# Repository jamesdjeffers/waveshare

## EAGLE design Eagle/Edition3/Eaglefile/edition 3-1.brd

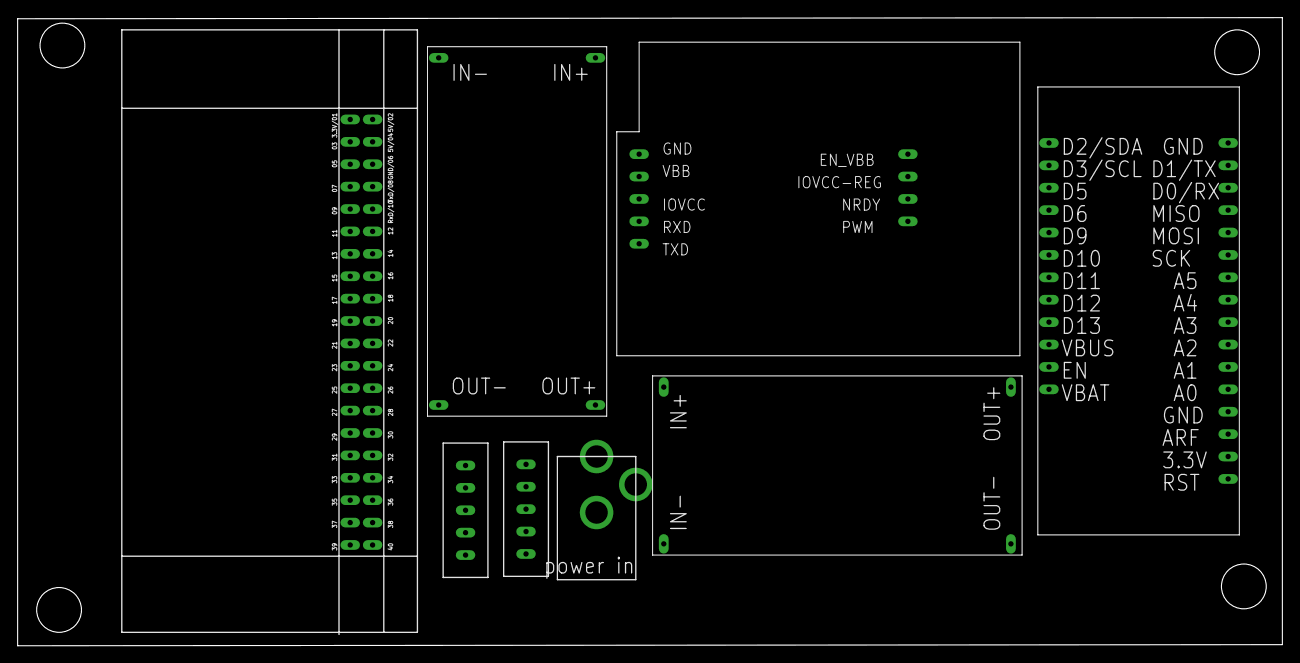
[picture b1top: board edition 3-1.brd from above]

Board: 2 copper layers, 143.4 x 71.2 mm, 8 parts (0 on the bottom side), 10 nets, no tracks yet.

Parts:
DCDC1, DCDC2: DCDC
FEATHER1: FEATHER
K96SENSOR1: K96SENSOR
PIN1, PIN2: PIN
U$1: POWER; POWERIN
U$2: RASPBERRYPI

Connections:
unnamed: DCDC1.P$2, DCDC2.P$2, K96SENSOR1.P$2, PIN1.P$1, U$1.P$1
unnamed: DCDC1.P$1, DCDC1.P$4, DCDC2.P$1, DCDC2.P$4, FEATHER1.P$13, K96SENSOR1.P$1, PIN1.P$2, U$1.P$2, U$1.P$3, U$2.P$3
unnamed: FEATHER1.P$6, K96SENSOR1.P$4
unnamed: DCDC1.P$3, FEATHER1.P$12
unnamed: FEATHER1.P$7, K96SENSOR1.P$5
unnamed: FEATHER1.P$4, K96SENSOR1.P$8
unnamed: FEATHER1.P$9, PIN2.P$1, U$2.P$5
unnamed: FEATHER1.P$3, K96SENSOR1.P$6
unnamed: FEATHER1.P$27, K96SENSOR1.P$3
unnamed: FEATHER1.P$8, PIN2.P$2, U$2.P$4

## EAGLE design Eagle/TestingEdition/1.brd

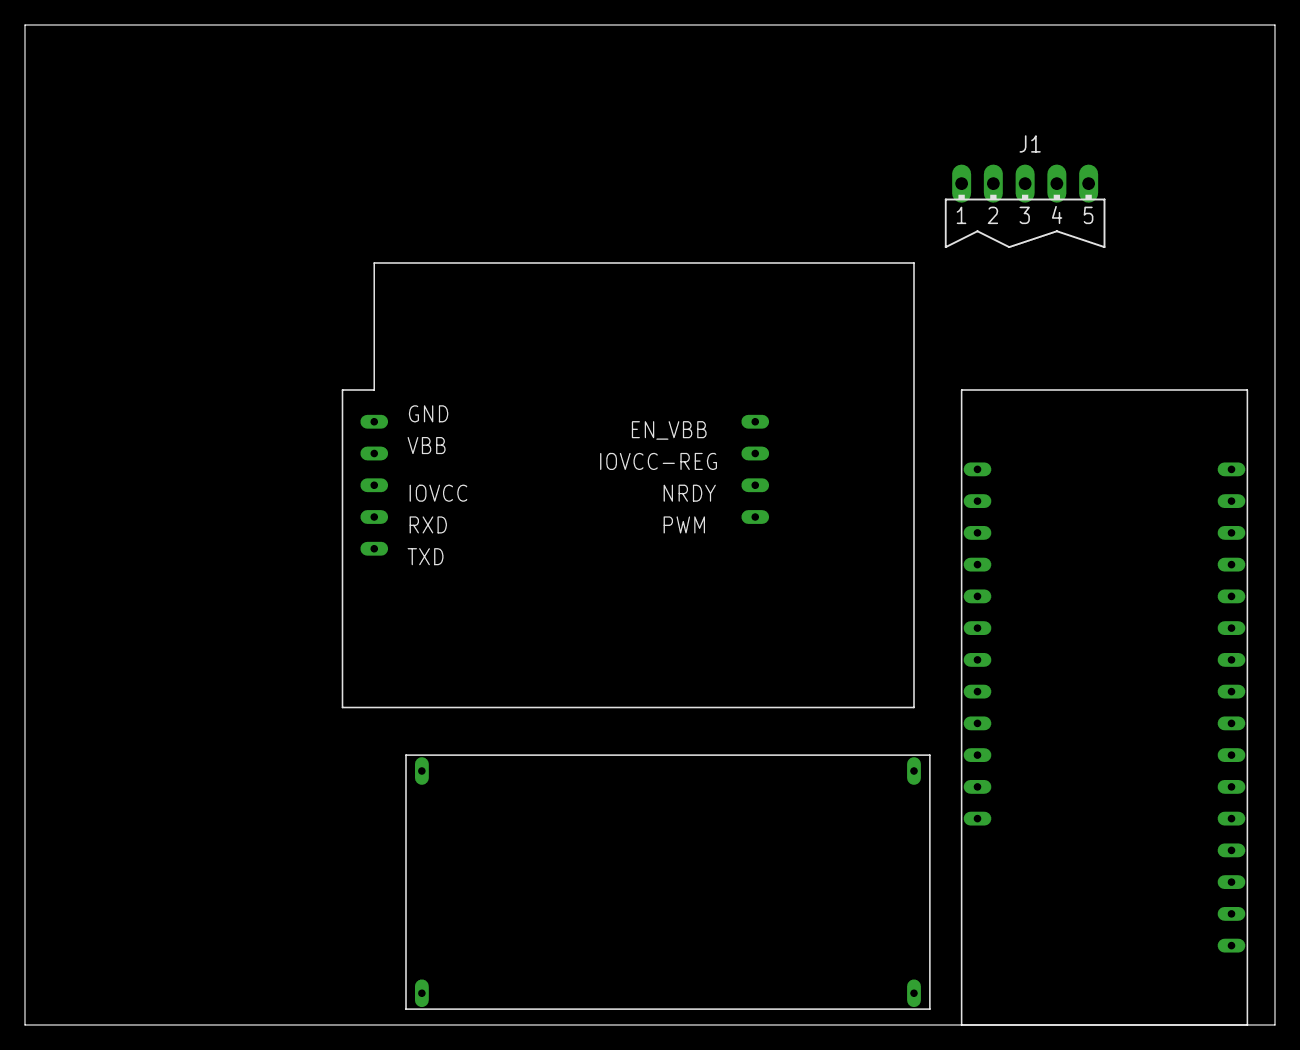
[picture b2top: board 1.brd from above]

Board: 2 copper layers, 100.0 x 80.0 mm, 4 parts (0 on the bottom side), 7 nets, no tracks yet.

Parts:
DCDC1: DCDC
FEATHER1: FEATHER
J1: JU05
K96SENSOR1: K96SENSOR

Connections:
unnamed: DCDC1.P$1, J1.5
unnamed: DCDC1.P$3, DCDC1.P$4, FEATHER1.P$28, J1.4, K96SENSOR1.P$1
unnamed: FEATHER1.P$6, K96SENSOR1.P$6
unnamed: DCDC1.P$2, FEATHER1.P$14
unnamed: FEATHER1.P$4, K96SENSOR1.P$4
unnamed: FEATHER1.P$5, K96SENSOR1.P$5
unnamed: FEATHER1.P$7, K96SENSOR1.P$8

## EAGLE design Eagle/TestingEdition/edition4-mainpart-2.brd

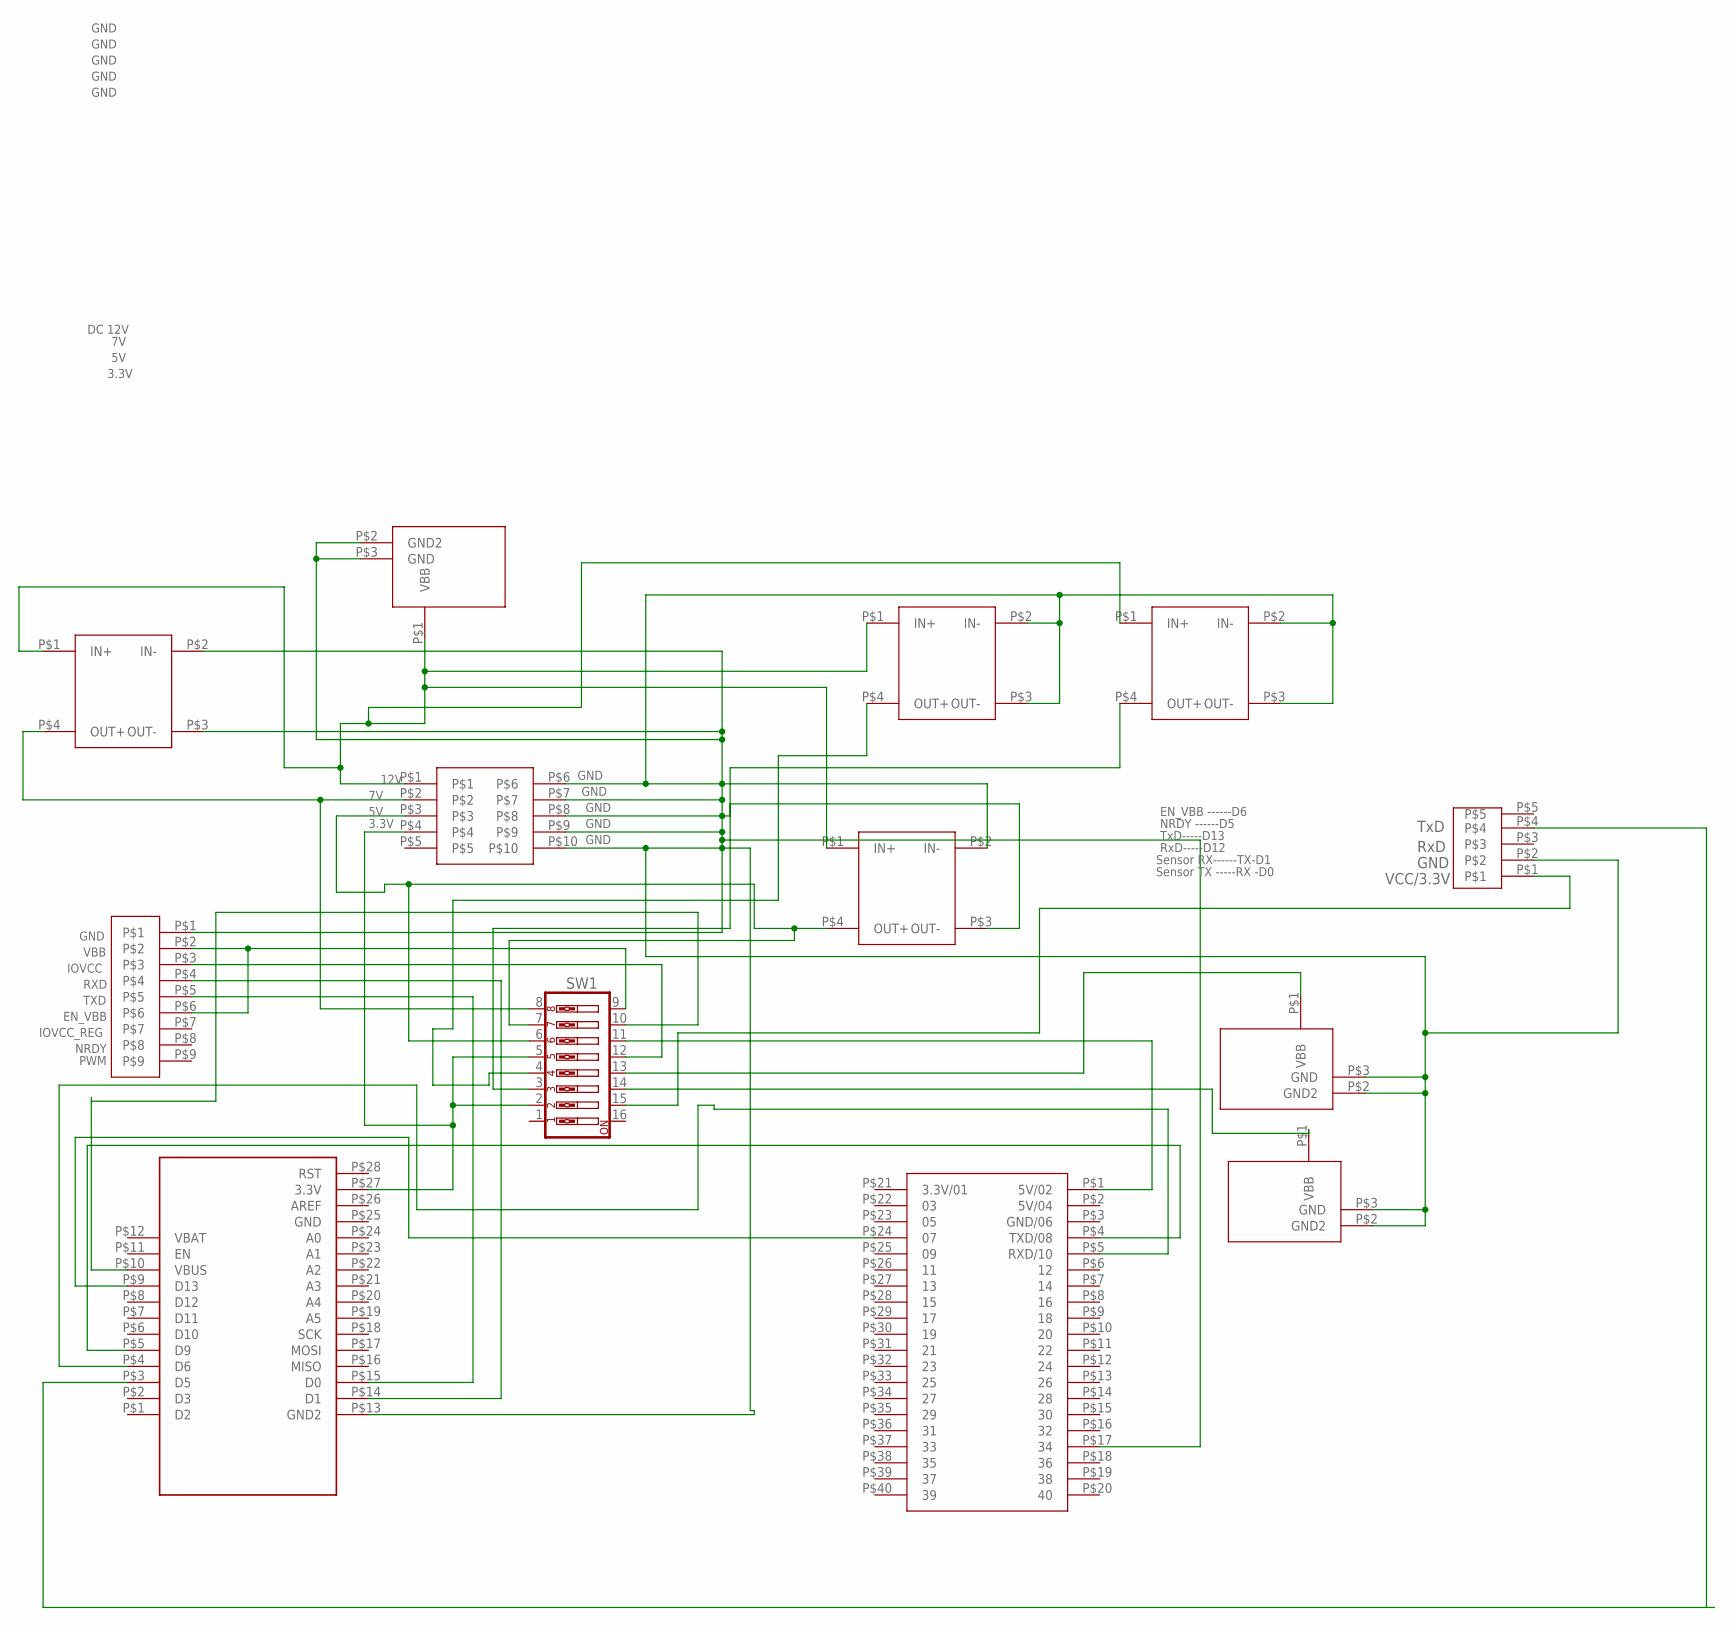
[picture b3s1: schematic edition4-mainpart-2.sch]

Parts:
SW1: SW_DIP-8; EDG-08
U$1, U$2, U$6, U$7: MH-MINI-360
U$3, U$4, U$5: POWER; POWERIN
U$8: PIN
U$10: FEATHER
U$11: RASPBERRYPI
U$14: 2X5FEET
U$15: 9FEETPIN

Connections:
unnamed: SW1.10, U$10.P$10 (VBUS)
unnamed: SW1.3, U$7.P$4 (OUT+)
unnamed: SW1.2, SW1.5, U$10.P$27 (3.3V), U$14.P$4
unnamed: SW1.8, U$6.P$4 (OUT+), U$14.P$2
unnamed: SW1.9, U$15.P$2, U$15.P$6
unnamed: U$8.P$4, U$10.P$3 (D5)
unnamed: SW1.12, U$15.P$3
unnamed: U$10.P$14 (D1), U$15.P$4
unnamed: U$10.P$15 (D0), U$15.P$5
unnamed: U$10.P$9 (D13), U$11.P$24 (07)
unnamed: SW1.6, SW1.7, U$2.P$4 (OUT+), U$14.P$3
unnamed: SW1.11, U$11.P$1 (5V/02)
unnamed: SW1.15, U$8.P$1
unnamed: SW1.13, U$5.P$1 (VBB)
unnamed: U$10.P$5 (D9), U$11.P$4 (TXD/08)
unnamed: U$10.P$4 (D6), U$11.P$5 (RXD/10)
unnamed: SW1.4, U$1.P$4 (OUT+)
unnamed: U$1.P$1 (IN+), U$2.P$1 (IN+), U$3.P$1 (VBB), U$6.P$1 (IN+), U$7.P$1 (IN+), U$14.P$1
unnamed: SW1.14, U$4.P$1 (VBB)
unnamed: U$1.P$2 (IN-), U$1.P$3 (OUT-), U$2.P$2 (IN-), U$2.P$3 (OUT-), U$3.P$2 (GND2), U$3.P$3 (GND), U$4.P$2 (GND2), U$4.P$3 (GND), U$5.P$2 (GND2), U$5.P$3 (GND), U$6.P$2 (IN-), U$6.P$3 (OUT-), U$7.P$2 (IN-), U$7.P$3 (OUT-), U$8.P$2, U$10.P$13 (GND2), U$11.P$17 (34), U$14.P$6, U$14.P$7, U$14.P$8, U$14.P$9, U$14.P$10, U$15.P$1

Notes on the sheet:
GND
DC 12V
3.3V
Sensor RX------TX-D1
TxD-----D13
RxD-----D12
EN_VBB ------D6
NRDY ------D5
Sensor TX -----RX -D0
PWM
NRDY
IOVCC_REG
EN_VBB
TXD
RXD
IOVCC
VBB
12V
TxD
RxD
VCC/3.3V

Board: 2 copper layers, 13 parts (1 on the bottom side), 20 nets, no tracks yet.
